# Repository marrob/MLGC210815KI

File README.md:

# MLGC210815KI
Smart Logic Probe, Schematic, Demo project with KiCAD

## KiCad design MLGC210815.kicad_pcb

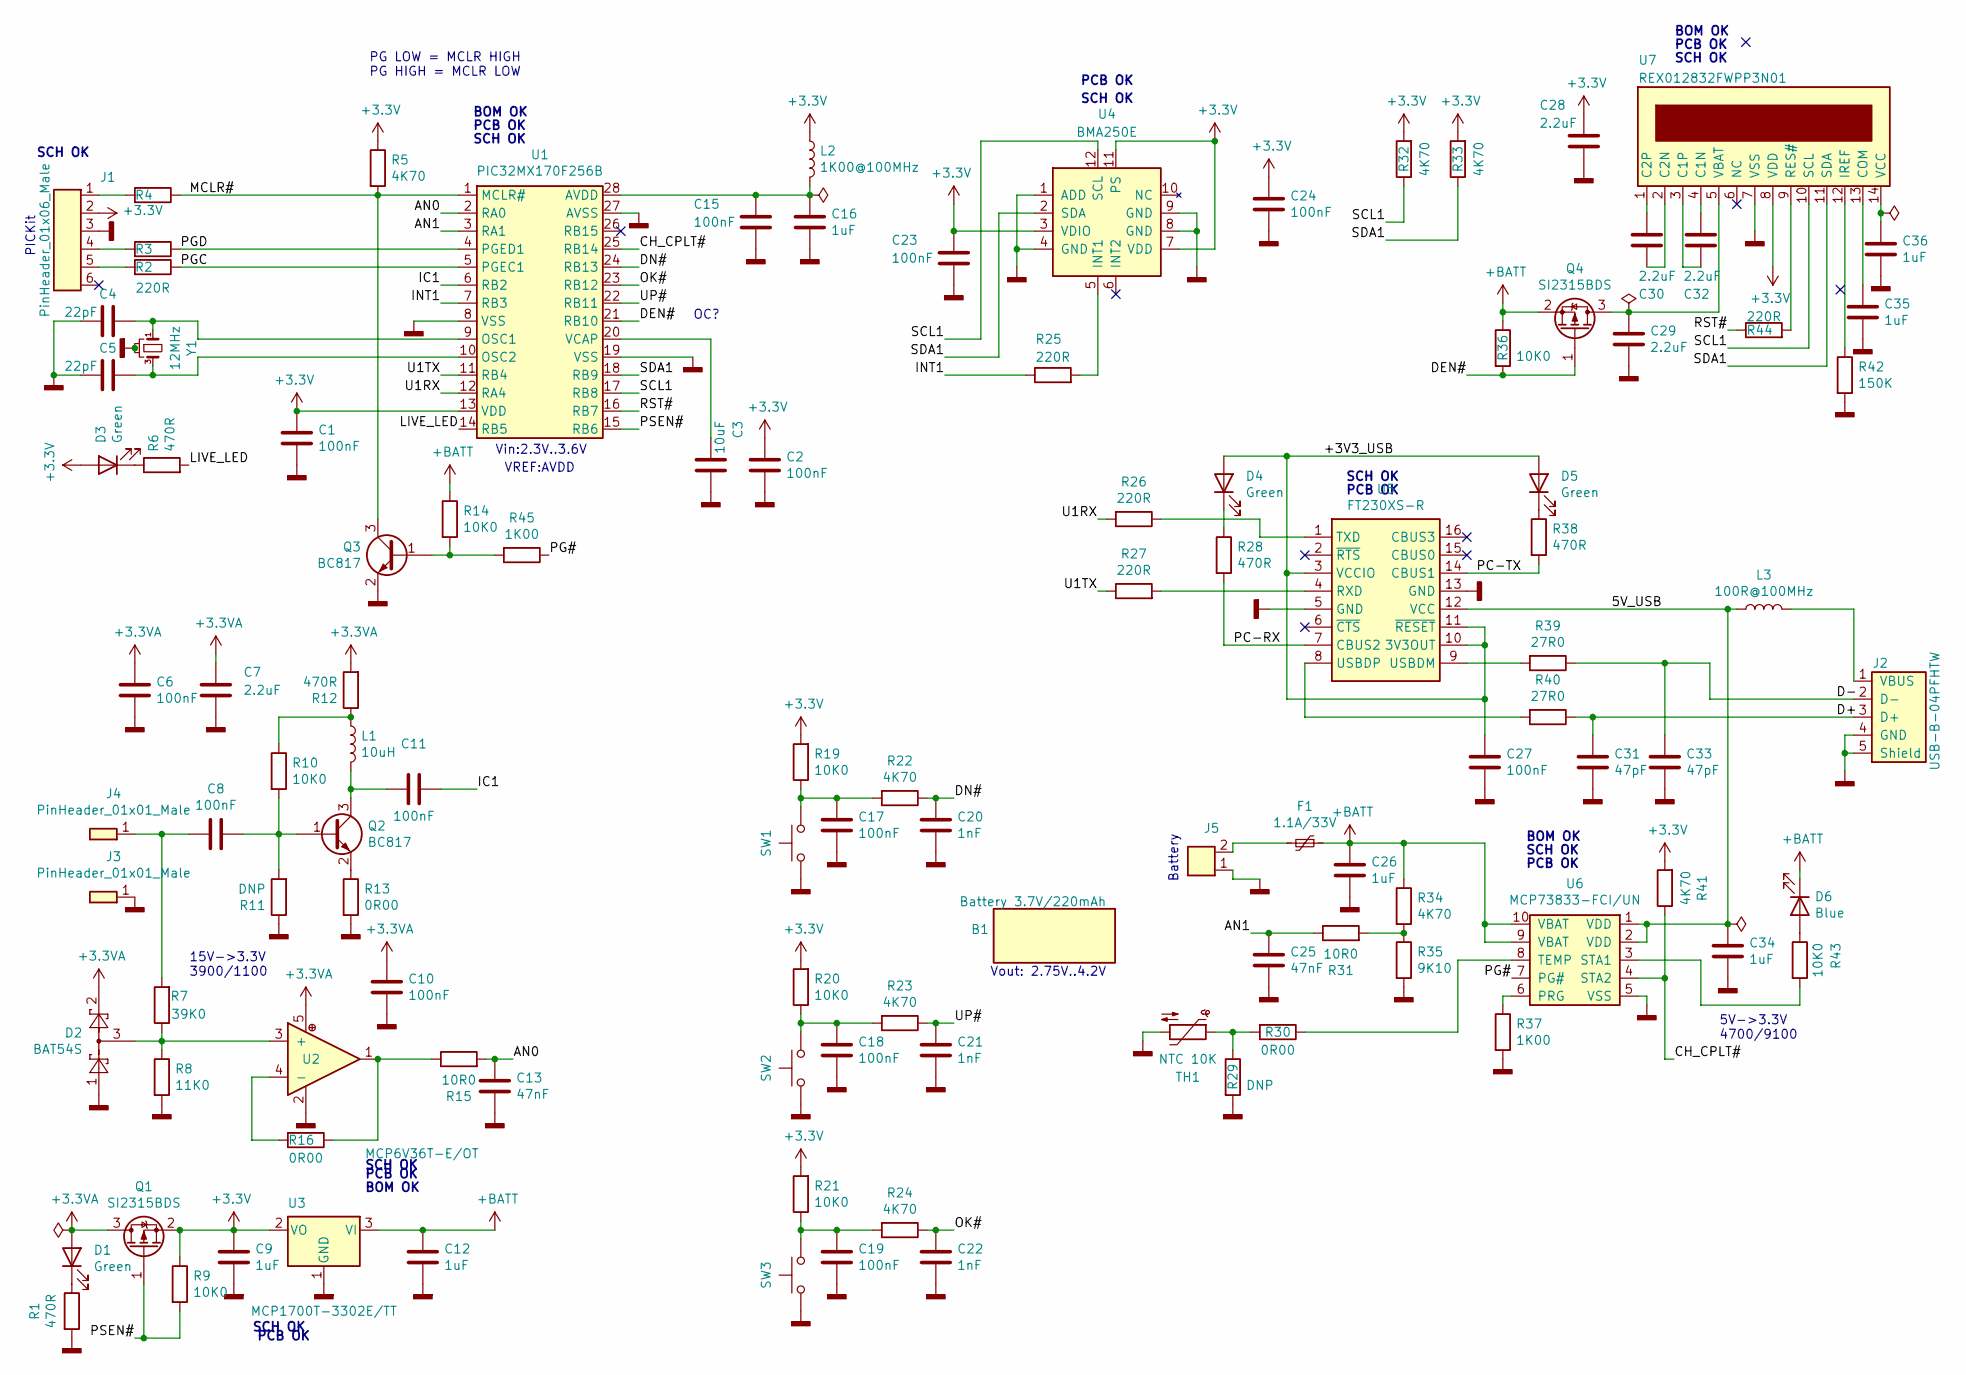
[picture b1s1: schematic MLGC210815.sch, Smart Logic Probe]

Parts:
B1: BATTERY_L402036; CELLEVIA_L402036; ManufacturerPartNo L402036
C1, C2, C6, C8, C10, C11, C15, C17, C18, C19, C23, C24, C27: Capacitator_0603_100nF_X7R; C_0603; ManufacturerPartNo CC0603KRX7R9BB104
C3: Capacitator_0603_10uF_X5R; C_0603; ManufacturerPartNo GRM188R61A106KE69D
C4, C5: Capacitator_0603_22pF_NP0; C_0603; ManufacturerPartNo CC0603JRNP09BN220;
C7, C28, C29, C30, C32: Capacitator_0603_2.2uF_X5R; C_0603; ManufacturerPartNo X225K6R3CT;
C9, C12, C16, C26, C34, C35, C36: Capacitator_0603_1uF_X7R; C_0603; ManufacturerPartNo CC0603KRX7R7BB105;
C13, C25: Capacitator_0603_47nF_X7R; C_0603; ManufacturerPartNo 0603B473K500NT;
C20, C21, C22: Capacitator_0603_1nF_NP0; C_0603; ManufacturerPartNo CC0603JRNP09BN102;
C31, C33: Capacitator_0603_47pF_X7R; C_0603; ManufacturerPartNo CC0603JRNP09BN470
D1, D3, D4, D5: LED_0603_Green; LED_0603_GRE; ManufacturerPartNo HL-PST-1608U51GC
D2: DIODE_BAT54S; SOT-23; ManufacturerPartNo BAT54S;
D6: LED_0603_Blue; LED_0603_BLU; ManufacturerPartNo HL-PST-1608H203BC;
F1: Polyfuse_1812_1100mA_33V; F_1812; ManufacturerPartNo 1812L110/33MR
J1: PinHeader_01x06_Male; PinHeader_1x06_P2.54mm_Vertical; ManufacturerPartNo PHSS-40-6/3
J2: USB-B-04PFHTW; T-T_USB-B-04PFHTW; ManufacturerPartNo USB-A-S04PFHTW;MX-67068-8000;
J3, J4: PinHeader_01x01_Male; PinHeader_1x01_P2.54mm_Horizontal; ManufacturerPartNo PHSS-40-6/3
J5: PinHeader_01x02_Male; PinHeader_1x02_P2.54mm_Vertical; ManufacturerPartNo PHSS-40-6/3
L1: Inductor_0805_10uH; L_0805; ManufacturerPartNo LQM21FN100N00L
L2: Filter_0805_BLM21A102SPT; L_0805; ManufacturerPartNo BLM21A102SPT
L3: Filter_0603_CB03YTYH101; L_0603; ManufacturerPartNo CB03YTYH101
Q1, Q4: P-MOSFET_SI2315BDS-T1-E3; SOT-23; ManufacturerPartNo SI2315BDS-T1-E3
Q2, Q3: NPN_BC817; SOT-23; ManufacturerPartNo BC817-25LT1G
R1, R6, R12, R28, R38: Resistor_0603_470R; R_0603; ManufacturerPartNo WR06X4700FTL
R2, R3, R4, R25, R26, R27, R44: Resistor_0603_220R; R_0603; ManufacturerPartNo CR-03FL7--220R 0.1W
R5, R22, R23, R24, R32, R33, R34, R41: Resistor_0603_4K70; R_0603; ManufacturerPartNo CQ0603-4K7-1%;
R7: Resistor_0603_39K0; R_0603; ManufacturerPartNo CRCW060339K0FKTABC
R8: Resistor_0603_11K0; R_0603; ManufacturerPartNo Viking Tech Corp.
R9, R10, R14, R19, R20, R21, R36, R43: Resistor_0603_10K0; R_0603; ManufacturerPartNo CR16-1002-FK
R11, R29: Resistor_0603_R_DNP; R_0603
R13, R16, R30: Resistor_0603_0R00; R_0603; ManufacturerPartNo RC0603JR-100RL;
R15, R31: Resistor_0603_10R0; R_0603; ManufacturerPartNo Viking Tech Corp.
R35: Resistor_0603_9K10; R_0603; ManufacturerPartNo CRCW06039K10FKTABC
R37, R45: Resistor_0603_1K00; R_0603; ManufacturerPartNo CR-03FL7----1K 0.1W
R39, R40: Resistor_0603_27R0; R_0603; ManufacturerPartNo CR-03FL7---27R 0.1W
R42: Resistor_0603_150K; R_0603; ManufacturerPartNo CR-03FL7--150K 0.1W
SW1, SW2, SW3: Switch-Tact_OMRON-B3F-3100; OMRON_B3F-3100; ManufacturerPartNo B3F-3100
TH1: NTC_0603_10K; R_0603; ManufacturerPartNo NTC0603-10K-B2;
U1: PIC32MX170F256B-ISS; SSOP-28; ManufacturerPartNo PIC32MX170F256B-I/SS
U2: OPA_MCP6V36T-E_OT; SOT-23-5; ManufacturerPartNo MCP6V36T-E/OT
U3: LDO_MCP1700T-3302E_TT; SOT-23; ManufacturerPartNo MCP1700T-3302E/TT
U4: SENSOR_BMA250E; LGA-12; ManufacturerPartNo BMA250E
U5: INTERFACE_FT230XS; SSOP-16; ManufacturerPartNo FT230XS-R
U6: BATTERY_MCP73833-FCI_UN; MSOP-10; ManufacturerPartNo MCP73833-FCI/UN
U7: DISPLAY_REX012832FWPP3N01; RAYSTAR_REX012832; ManufacturerPartNo REX012832FWPP3N00001
Y1: Crystal_SMD3225_12MHz; Crystal_SMD_3225; ManufacturerPartNo SMD/NXK-32 12MHz

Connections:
+3.3VA: C6.1, C7.1, C10.1, D1.2 (A), D2.2, Q1.3 (D), R12.2, U2.5
+3V3: C1.1, C2.1, C9.1, C23.1, C24.1, C28.1, D3.2 (A), J1.2, L2.1, Q1.2 (S), R5.1, R9.1, R19.2, R20.2, R21.2, R32.2, R33.2, R41.2, U1.13 (VDD), U3.2 (VO), U4.3 (VDIO), U4.7 (VDD), U4.11 (PS), U7.8 (VDD)
+BATT: C12.1, C26.1, D6.1 (K), F1.1, Q4.2 (S), R14.1, R34.1, R36.1, U3.3 (VI), U6.9 (VBAT), U6.10 (VBAT)
/5V_USB: C34.1, L3.1, U5.12 (VCC), U6.1 (VDD), U6.2 (VDD)
/+3V3_USB: C27.1, D4.2 (A), D5.2 (A), U5.3 (VCCIO), U5.10 (3V3OUT), U5.11 (~RESET)
/AN0: C13.1, R15.2, U1.2 (RA0)
/AN1: C25.1, R31.1, U1.3 (RA1)
/CH_CPLT#: R41.1, U1.25 (RB14), U6.4 (STA2)
/D+: C31.1, J2.3 (D+), R40.1
/D-: C33.1, J2.2 (D-), R39.1
/DEN#: Q4.1 (G), R36.2, U1.21 (RB10)
/DN#: C20.1, R22.1, U1.24 (RB13)
/IC1: C11.1, U1.6 (RB2)
/INT1: R25.1, U1.7 (RB3)
/LIVE_LED: R6.2, U1.14 (RB5)
/MCLR#: Q3.3 (C), R4.1, R5.2, U1.1 (MCLR#)
/OK#: C22.1, R24.1, U1.23 (RB12)
/PC-RX: R28.2, U5.7 (CBUS2)
/PC-TX: R38.2, U5.14 (CBUS1)
/PG#: R45.1, U6.7 (PG#)
/PGC: R2.1, U1.5 (PGEC1)
/PGD: R3.1, U1.4 (PGED1)
/PSEN#: Q1.1 (G), R9.2, U1.15 (RB6)
/RST#: R44.1, U1.16 (RB7)
/SCL1: R32.1, U1.17 (RB8), U4.12 (SCL), U7.10 (SCL)
/SDA1: R33.1, U1.18 (RB9), U4.2 (SDA), U7.11 (SDA)
/U1RX: R26.2, U1.12 (RA4)
/U1TX: R27.1, U1.11 (RB4)
/UP#: C21.1, R23.1, U1.22 (RB11)
GNDD: C1.2, C2.2, C3.1, C4.2, C5.2, C6.2, C7.2, C9.2, C10.2, C12.2, C13.2, C15.2, C16.2, C17.2, C18.2, C19.2, C20.2, C21.2, C22.2, C23.2, C24.2, C25.2, C26.2, C27.2, C28.2, C29.2, C31.2, C33.2, C34.2, C35.2, C36.2, D2.1, J1.3, J2.4 (GND), J2.5 (Shield), J3.1, J5.1, Q3.2 (E), R1.2, R8.2, R11.1, R13.2, R29.2, R35.2, R37.2, R42.2, SW1.1, SW2.1, SW3.1, TH1.2, U1.8 (VSS), U1.19 (VSS), U1.27 (AVSS), U2.2, U3.1 (GND), U4.1 (ADD), U4.4 (GND), U4.8 (GND), U4.9 (GND), U5.5 (GND), U5.13 (GND), U6.5 (VSS), U7.7 (VSS), Y1.2, Y1.4
unnamed: C3.2, U1.20 (VCAP)
unnamed: C4.1, U1.9 (OSC1), Y1.1
unnamed: C5.1, U1.10 (OSC2), Y1.3
unnamed: C8.1, Q2.1 (B), R10.2, R11.2
unnamed: C8.2, J4.1, R7.2
unnamed: C11.2, L1.2, Q2.3 (C)
unnamed: C15.1, C16.1, L2.2, U1.28 (AVDD)
unnamed: C17.1, R19.1, R22.2, SW1.2
unnamed: C18.1, R20.1, R23.2, SW2.2
unnamed: C19.1, R21.1, R24.2, SW3.2
unnamed: C29.1, Q4.3 (D), U7.5 (VBAT)
unnamed: C30.1, U7.1 (C2P)
unnamed: C30.2, U7.2 (C2N)
unnamed: C32.1, U7.4 (C1N)
unnamed: C32.2, U7.3 (C1P)
unnamed: C35.1, U7.13 (COM)
unnamed: C36.1, U7.14 (VCC)
unnamed: D1.1 (K), R1.1
unnamed: D2.3, R7.1, R8.1, U2.3 (+)
unnamed: D3.1 (K), R6.1
unnamed: D4.1 (K), R28.1
unnamed: D5.1 (K), R38.1
unnamed: D6.2 (A), R43.1
unnamed: F1.2, J5.2
unnamed: J1.1, R4.2
unnamed: J1.4, R3.2
unnamed: J1.5, R2.2
unnamed: J2.1 (VBUS), L3.2
unnamed: L1.1, R10.1, R12.1
unnamed: Q2.2 (E), R13.1
unnamed: Q3.1 (B), R14.2, R45.2
unnamed: R15.1, R16.1, U2.1
unnamed: R16.2, U2.4 (-)
unnamed: R25.2, U4.5 (INT1)
unnamed: R26.1, U5.1 (TXD)
unnamed: R27.2, U5.4 (RXD)
unnamed: R29.1, R30.2, TH1.1
unnamed: R30.1, U6.8 (TEMP)
unnamed: R31.2, R34.2, R35.1
unnamed: R37.1, U6.6 (PRG)
unnamed: R39.2, U5.9 (USBDM)
unnamed: R40.2, U5.8 (USBDP)
unnamed: R42.1, U7.12 (IREF)
unnamed: R43.2, U6.3 (STA1)
unnamed: R44.2, U7.9 (RES#)

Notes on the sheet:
Vout: 2.75V..4.2V
Vin:2.3V..3.6V
PICKit
OC?
VREF:AVDD
5V->3.3V 4700/9100
15V->3.3V 3900/1100
PG LOW = MCLR HIGH PG HIGH = MCLR LOW
Battery
SCH OK
PCB OK
BOM OK

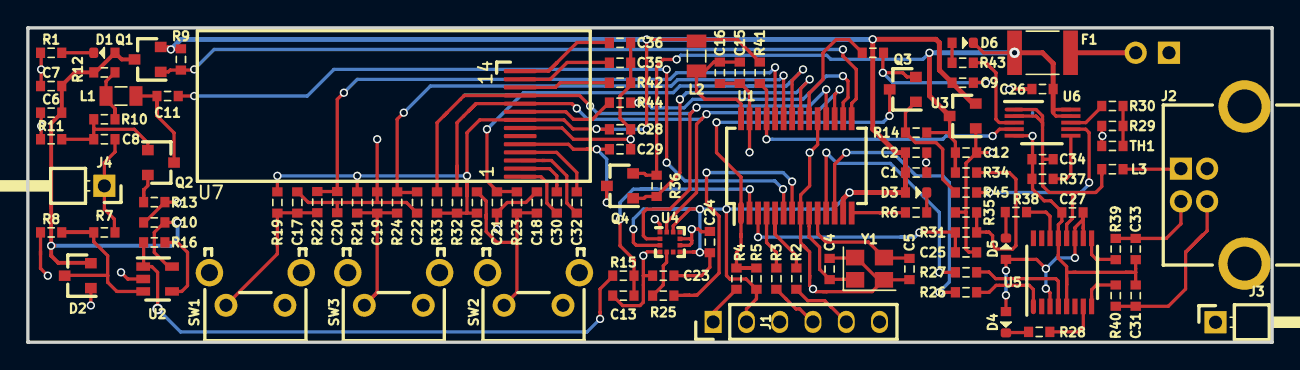
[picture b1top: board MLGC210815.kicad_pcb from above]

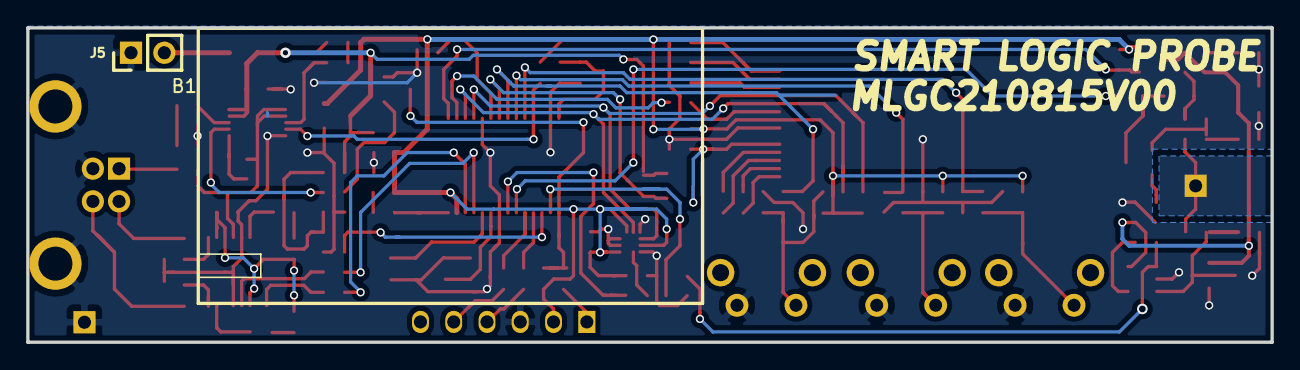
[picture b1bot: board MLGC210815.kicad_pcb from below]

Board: 2 copper layers, 95.0 x 24.0 mm, 110 parts (2 on the bottom side), 75 nets.

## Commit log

2021-08-26 first
2021-10-04 remove doc files
